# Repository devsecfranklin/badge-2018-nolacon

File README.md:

##  NolaCon 2018

[Check the Wiki for How To Use](https://github.com/devsecfranklin/badge-2018-nolacon/wiki)

## Created by

Будущее подпольной кибер-безопасности

- Hardware: [@thedevilsvoice](mailto:thedevilsvoice@protonmail.ch)
- Software: [@thedevilsvoice](mailto:thedevilsvoice@protonmail.ch)

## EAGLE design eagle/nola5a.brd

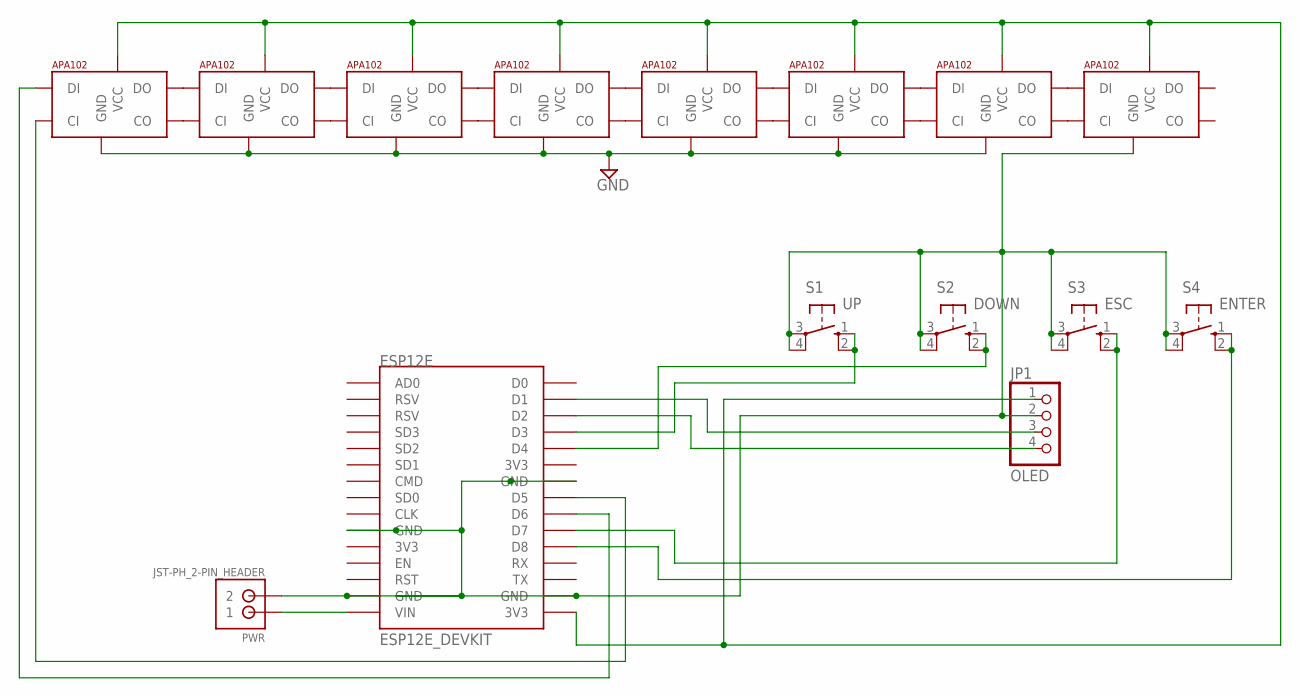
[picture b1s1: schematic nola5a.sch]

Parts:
ESP12E: ESP12E_DEVKIT
JP1: OLED; 1X04
LED1, LED2, LED3, LED4, LED5, LED6, LED7, LED8: APA1025050; APA102_5050
PWR: JST-PH_2-PIN_HEADER; JST_B2B-PH_HEADER
S1: UP; B3F-10XX
S2: DOWN; B3F-10XX
S3: ESC; B3F-10XX
S4: ENTER; B3F-10XX

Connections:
GND: ESP12E.GND@0 (GND), ESP12E.GND@1 (GND), ESP12E.GND@2 (GND), ESP12E.GND@3 (GND), JP1.2, LED1.6 (GND), LED2.6 (GND), LED3.6 (GND), LED4.6 (GND), LED5.6 (GND), LED6.6 (GND), LED7.6 (GND), LED8.6 (GND), PWR.P2 (2), S1.3, S1.4 (P1), S2.3, S2.4 (P1), S3.3, S3.4 (P1), S4.3, S4.4 (P1)
unnamed: LED1.3 (DO), LED2.4 (DI)
unnamed: LED1.2 (CO), LED2.5 (CI)
unnamed: LED2.3 (DO), LED3.4 (DI)
unnamed: LED2.2 (CO), LED3.5 (CI)
unnamed: LED3.3 (DO), LED4.4 (DI)
unnamed: LED3.2 (CO), LED4.5 (CI)
unnamed: LED4.3 (DO), LED5.4 (DI)
unnamed: LED4.2 (CO), LED5.5 (CI)
unnamed: LED5.3 (DO), LED6.4 (DI)
unnamed: LED5.2 (CO), LED6.5 (CI)
unnamed: LED6.3 (DO), LED7.4 (DI)
unnamed: LED6.2 (CO), LED7.5 (CI)
unnamed: LED7.3 (DO), LED8.4 (DI)
unnamed: LED7.2 (CO), LED8.5 (CI)
unnamed: ESP12E.D1, JP1.3
unnamed: ESP12E.3V3@2 (3V3), JP1.1, LED1.1 (VCC), LED2.1 (VCC), LED3.1 (VCC), LED4.1 (VCC), LED5.1 (VCC), LED6.1 (VCC), LED7.1 (VCC), LED8.1 (VCC)
unnamed: ESP12E.D2, JP1.4
unnamed: ESP12E.D6, LED1.4 (DI)
unnamed: ESP12E.D5, LED1.5 (CI)
unnamed: ESP12E.D3, S1.1 (S), S1.2 (S1)
unnamed: ESP12E.D4, S2.1 (S), S2.2 (S1)
unnamed: ESP12E.D7, S3.1 (S), S3.2 (S1)
unnamed: ESP12E.D8, S4.1 (S), S4.2 (S1)
unnamed: ESP12E.VIN, PWR.P1 (1)

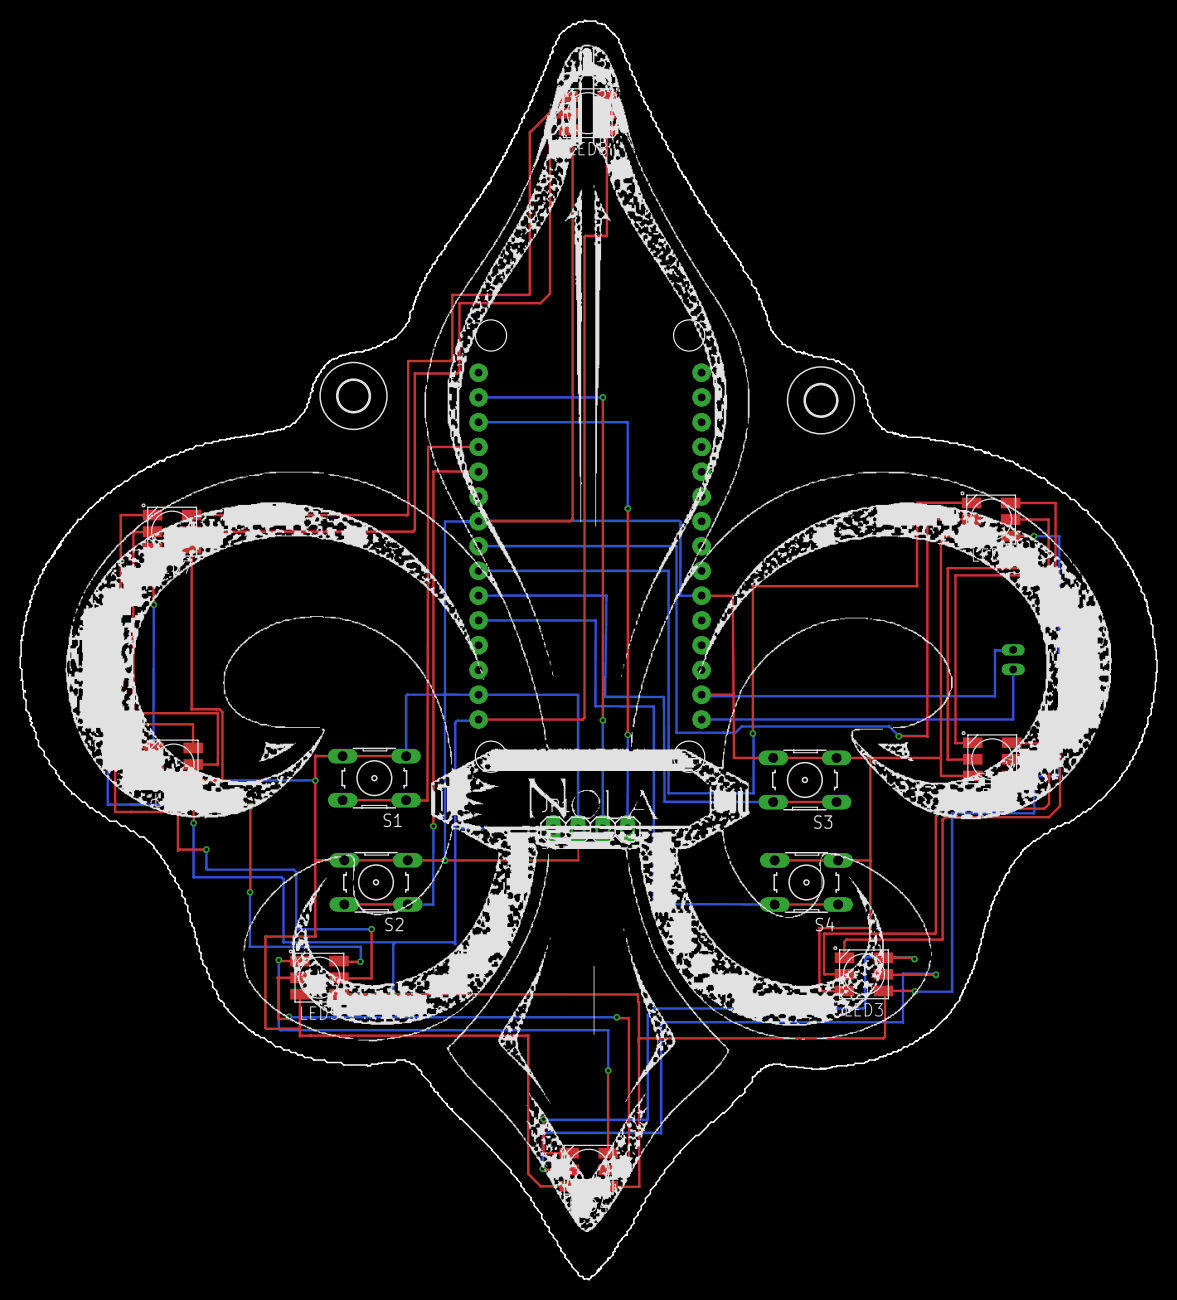
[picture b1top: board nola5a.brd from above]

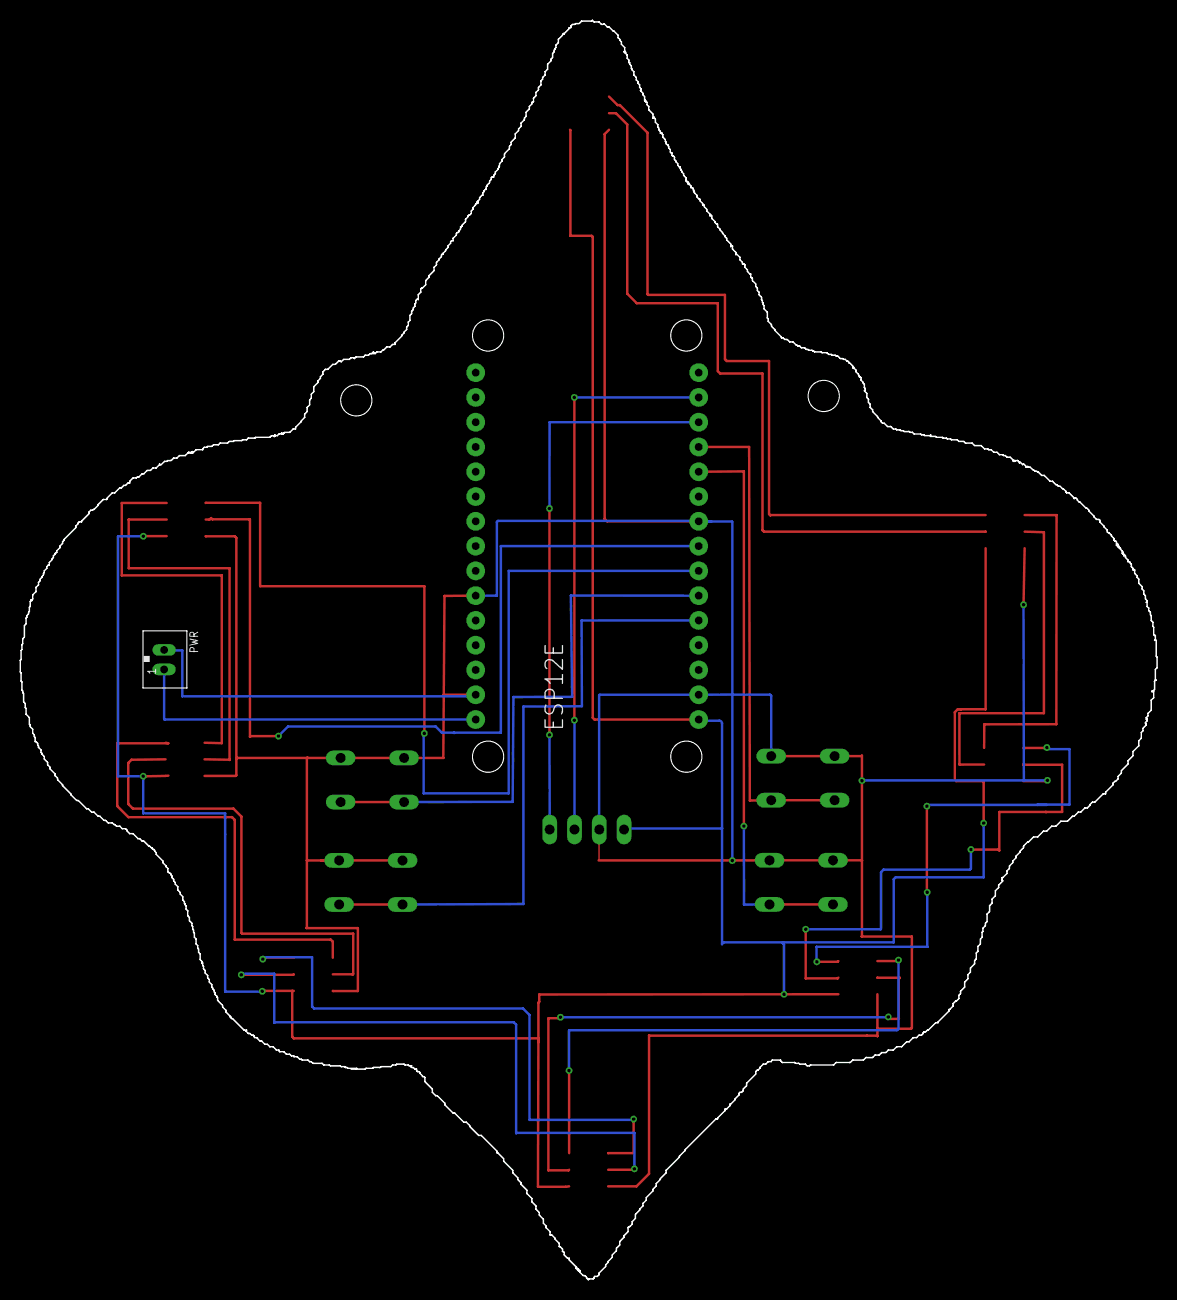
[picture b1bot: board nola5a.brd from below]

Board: 2 copper layers, 116.5 x 129.1 mm, 17 parts (2 on the bottom side), 25 nets.

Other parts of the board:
U$1, U$2: 3,2

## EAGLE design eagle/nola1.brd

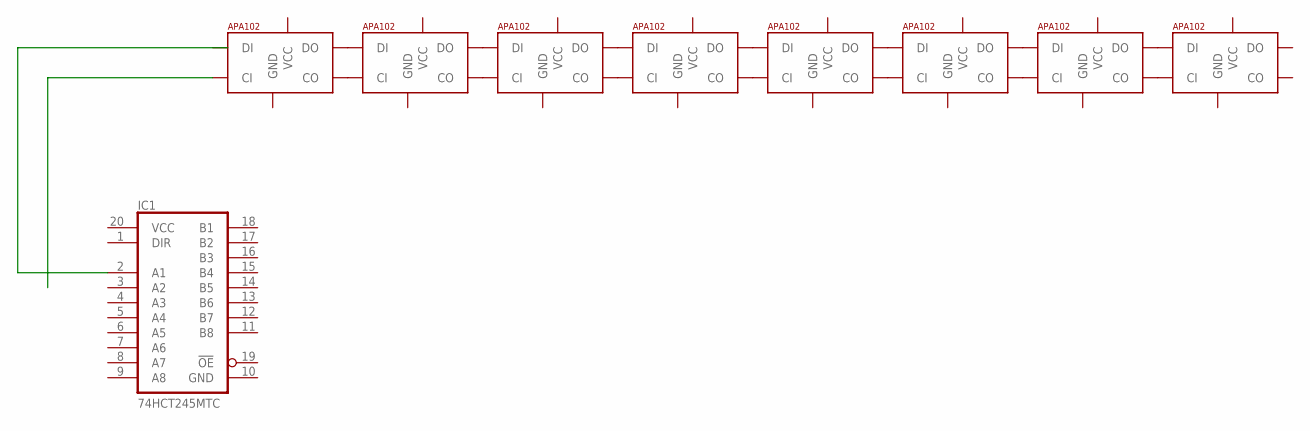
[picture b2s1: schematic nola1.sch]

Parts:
IC1: 74HCT245MTC; SSOP20
U$3, U$4, U$5, U$6, U$7, U$8, U$9, U$10: APA1025050; APA102_5050

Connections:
GND: IC1.10 (GND)
unnamed: U$3.3 (DO), U$4.4 (DI)
unnamed: U$3.2 (CO), U$4.5 (CI)
unnamed: U$4.3 (DO), U$5.4 (DI)
unnamed: U$4.2 (CO), U$5.5 (CI)
unnamed: U$5.3 (DO), U$6.4 (DI)
unnamed: U$5.2 (CO), U$6.5 (CI)
unnamed: U$6.3 (DO), U$7.4 (DI)
unnamed: U$6.2 (CO), U$7.5 (CI)
unnamed: U$7.3 (DO), U$8.4 (DI)
unnamed: U$7.2 (CO), U$8.5 (CI)
unnamed: U$8.3 (DO), U$9.4 (DI)
unnamed: U$8.2 (CO), U$9.5 (CI)
unnamed: U$9.3 (DO), U$10.4 (DI)
unnamed: U$9.2 (CO), U$10.5 (CI)
VCC: IC1.20 (VCC)

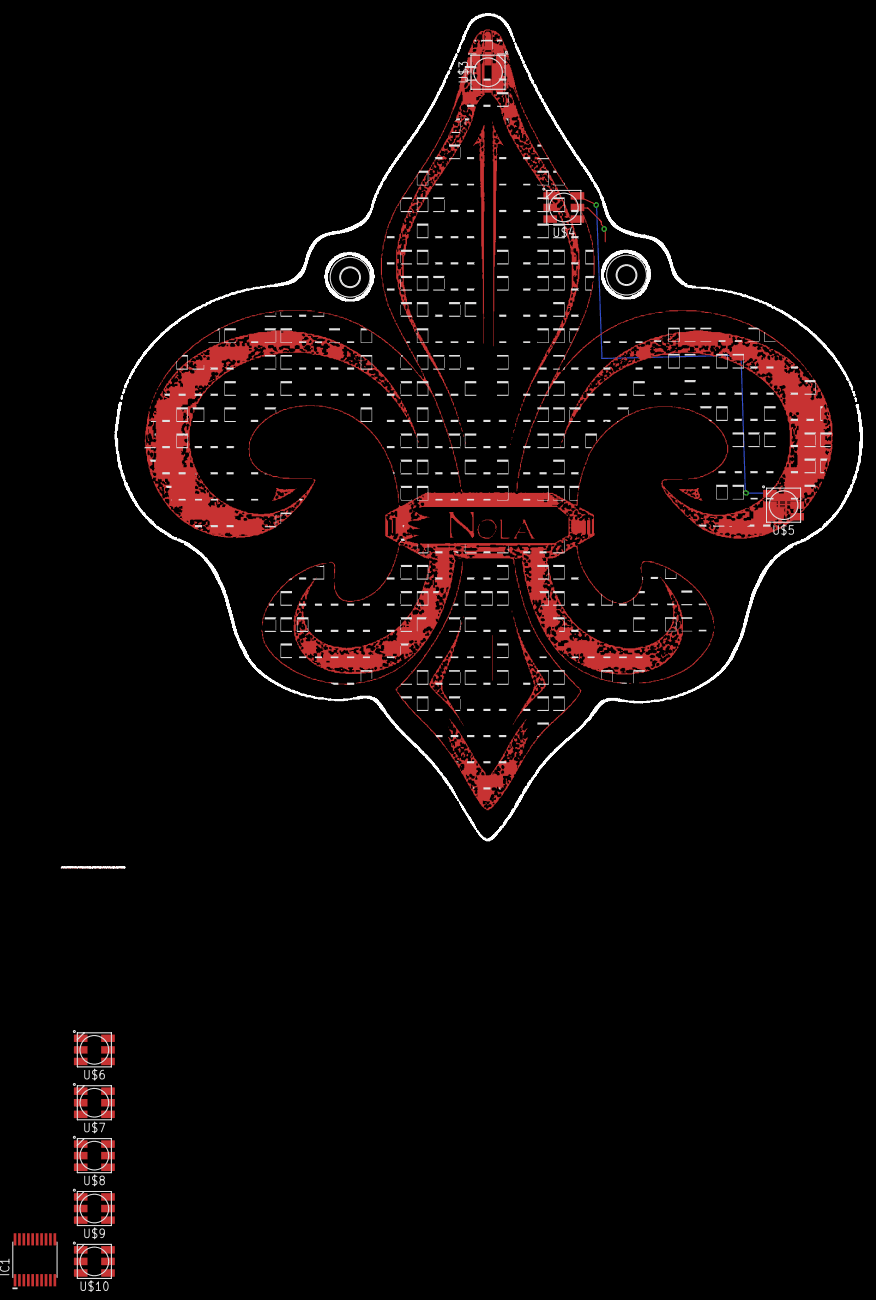
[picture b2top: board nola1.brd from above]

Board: 2 copper layers, 109.6 x 121.4 mm, 11 parts (0 on the bottom side), 14 nets.

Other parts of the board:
U$1, U$2: 2,8

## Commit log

2019-03-16 udpates
2019-03-16 tune travis.yml
2019-03-16 fix travis
2019-03-17 testing compact menu function
2019-03-17 update buttons
2019-03-17 mess with pong game
2019-05-19 cleanup
2019-05-19 mv files to src dir
2019-05-19 vscode
2019-05-19 missing double quote
2022-08-24 Add renovate.json
2022-08-24 Add .whitesource configuration file
2022-10-10 Add renovate.json (#20)
2022-10-10 Add .whitesource configuration file (#21)
2023-03-16 Update ubuntu Docker tag to v22
2024-04-26 Update ubuntu Docker tag to v24
2024-05-24 Update ubuntu Docker tag to v24 (#24)
2025-05-11 move renovate
2025-05-11 add in old files and refresh the repo
2025-05-11 add images
2025-05-11 refresh the repo (#25)
    * move renovate
    * add in old files and refresh the repo
    * add images
2025-05-11 update documentation
